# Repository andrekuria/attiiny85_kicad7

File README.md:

# ATtiny85 USB Interface PCB

This is a small embedded systems project showcasing an ATtiny85 microcontroller with USB connectivity

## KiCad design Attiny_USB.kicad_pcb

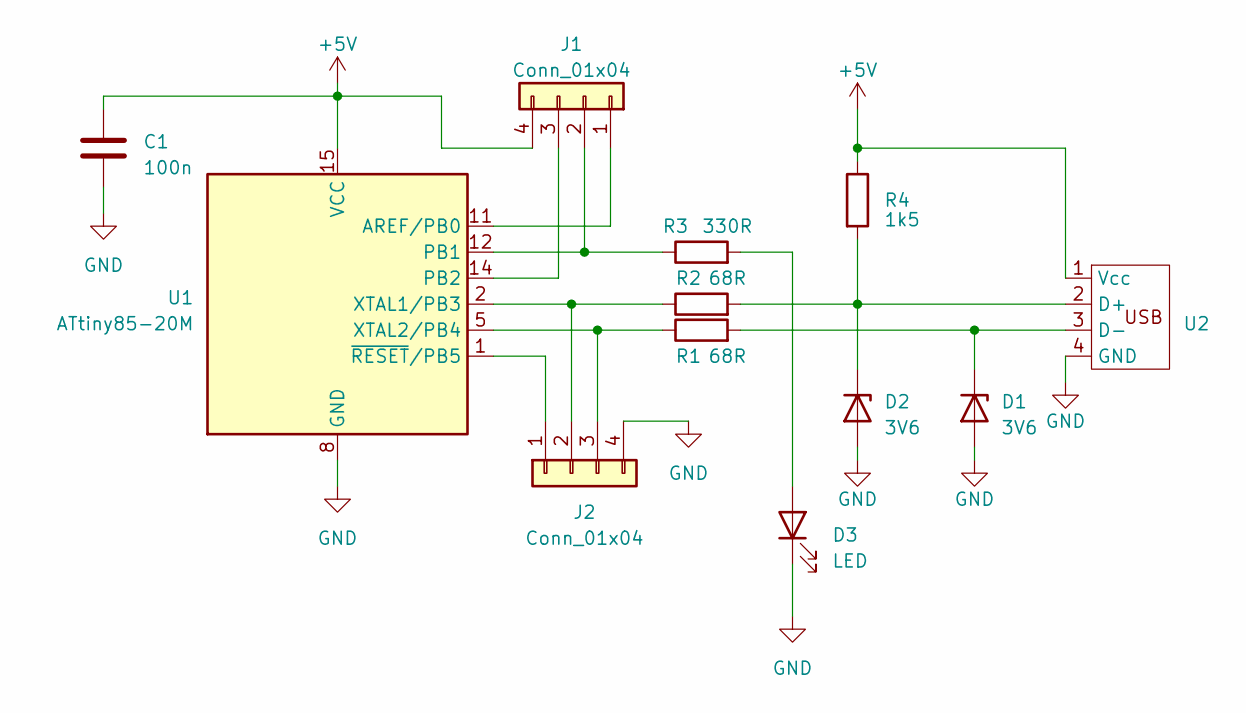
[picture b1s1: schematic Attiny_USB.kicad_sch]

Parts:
C1: 100n; C_1206_3216Metric_Pad1.33x1.80mm_HandSolder
D1, D2: 3V6; D_SOD-123
D3: LED; LED_0805_2012Metric
J1, J2: Conn_01x04; PinHeader_1x04_P2.54mm_Vertical
R1, R2: 68R; R_0805_2012Metric_Pad1.20x1.40mm_HandSolder
R3: 330R; R_0805_2012Metric_Pad1.20x1.40mm_HandSolder
R4: 1k5; R_0805_2012Metric_Pad1.20x1.40mm_HandSolder
U1: ATtiny85-20M; QFN-20-1EP_4x4mm_P0.5mm_EP2.6x2.6mm
U2: PCB_USB_conn

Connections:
+5V: C1.1, J1.4, R4.1, U1.15 (VCC), U2.1 (Vcc)
GND: C1.2, D1.2 (A), D2.2 (A), D3.1 (K), J2.4, U1.8 (GND), U1.21 (GND), U2.4 (GND)
unnamed: D1.1 (K), R1.2, U2.3 (D-)
unnamed: D2.1 (K), R2.2, R4.2, U2.2 (D+)
unnamed: D3.2 (A), R3.2
unnamed: J1.1, U1.11 (AREF/PB0)
unnamed: J1.2, R3.1, U1.12 (PB1)
unnamed: J1.3, U1.14 (PB2)
unnamed: J2.1, U1.1 (~RESET/PB5)
unnamed: J2.2, R2.1, U1.2 (XTAL1/PB3)
unnamed: J2.3, R1.1, U1.5 (XTAL2/PB4)

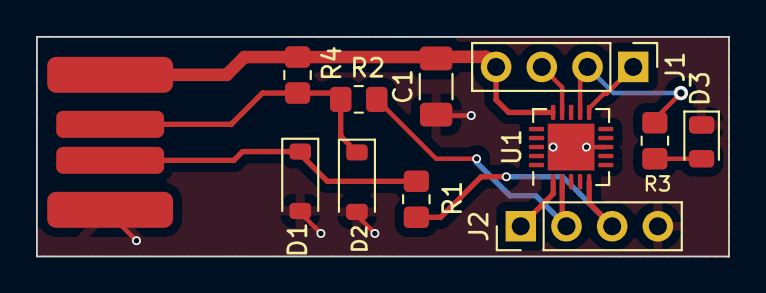
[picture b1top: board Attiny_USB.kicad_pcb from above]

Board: 2 copper layers, 38.4 x 12.2 mm, 12 parts (0 on the bottom side), 11 nets.
